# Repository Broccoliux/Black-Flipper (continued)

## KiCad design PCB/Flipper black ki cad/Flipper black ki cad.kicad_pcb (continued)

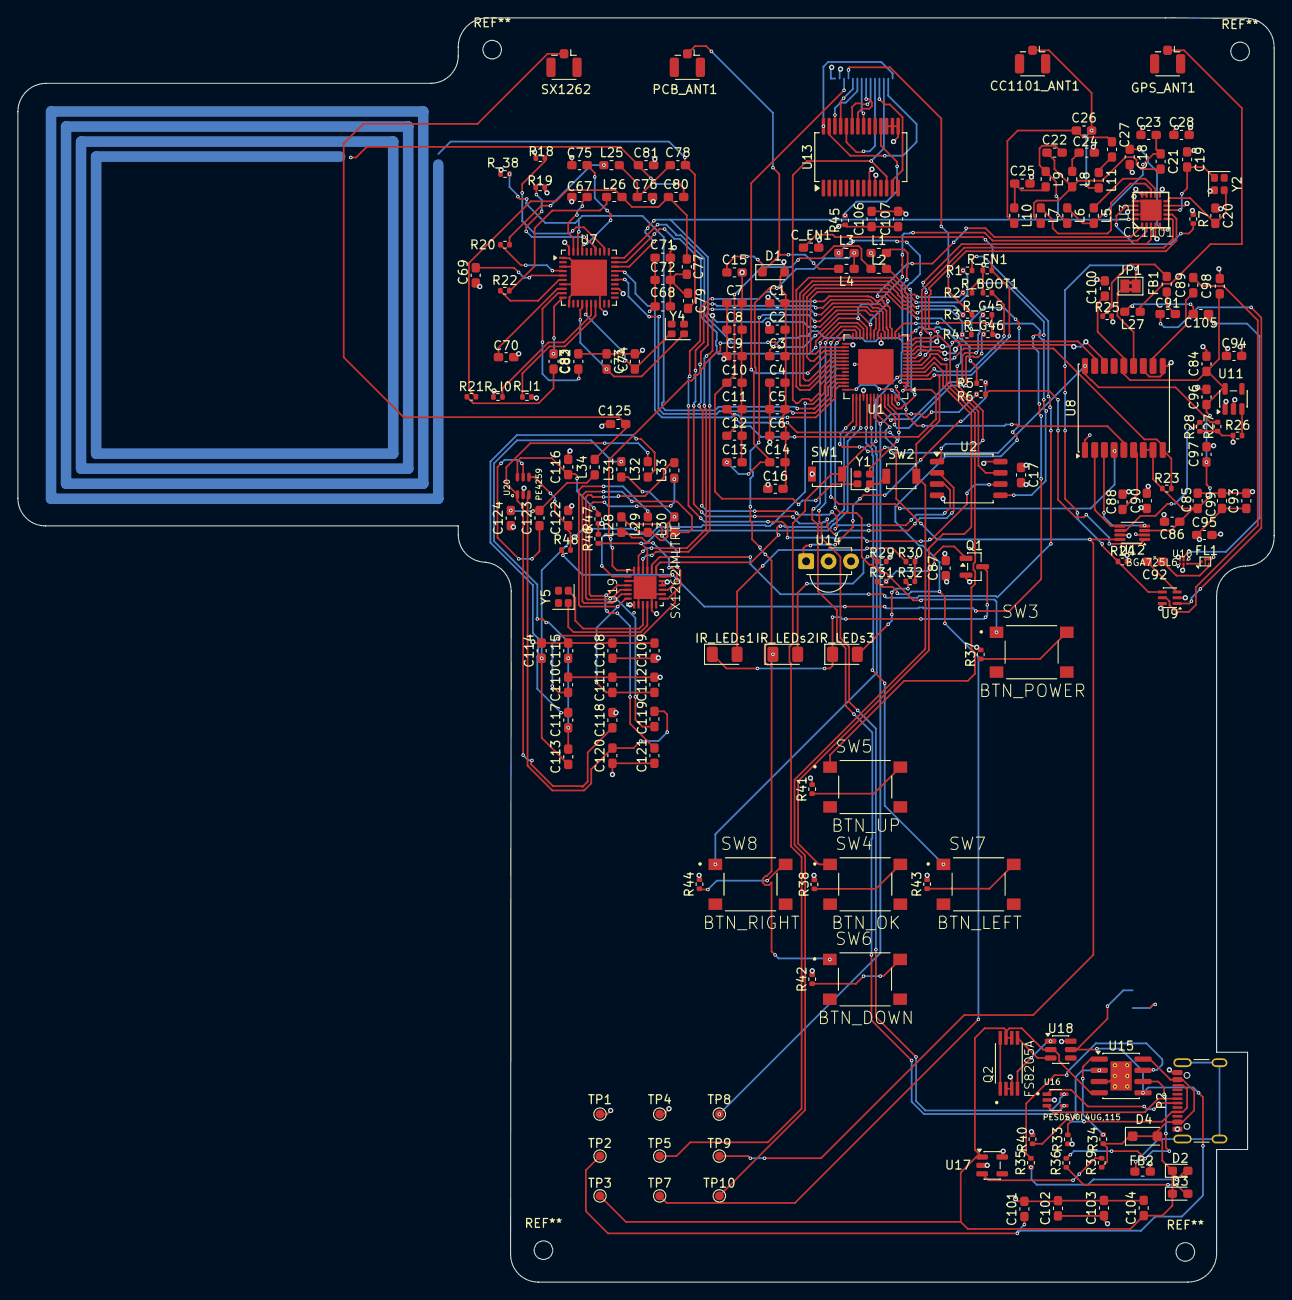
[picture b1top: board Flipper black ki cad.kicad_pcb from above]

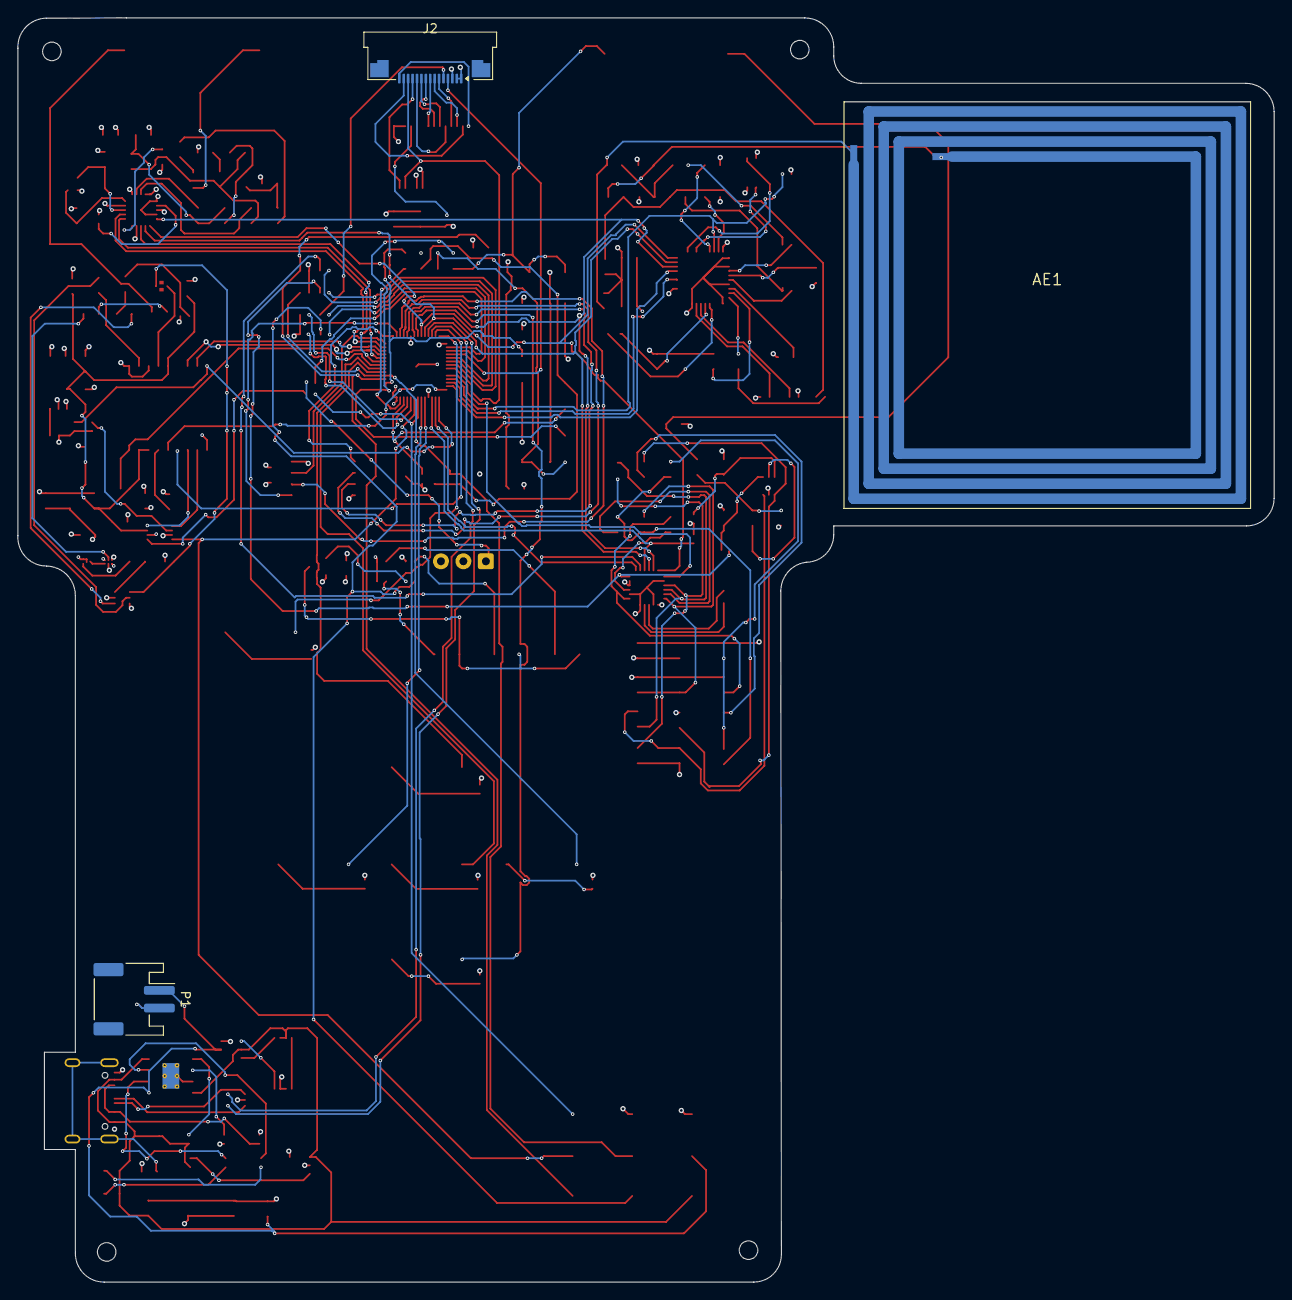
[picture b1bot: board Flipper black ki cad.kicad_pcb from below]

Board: 4 copper layers, 142.1 x 143.0 mm, 213 parts (3 on the bottom side), 169 nets.

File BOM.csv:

Reference,Qty,Value,link,cost
"C1,C2,C6,C7,C8,C17,C18,C67,C68,C69,C70,C71,C75,C84,C86,C87,C94,C96,C97,C98,C99,C100,C107,C109,C113,C121",26,100nf,,
"C3,C16,C101",3,0.1uf,,
"C4,C95,C102,C103,C104,C106",6,10uf,,
"C5,C9,C72,C85,C108,C_EN1",5,1uf,,
"C10,C11,C19,C20,C21,C22,C23,C24,C28",9,18pf,,
C12,1,1.8pf,,
C13,1,1.2pf,,
"C14,C25",2,1.0pf,,
"C15,C26,C27",3,1.5pf,,
"C74,C78,C80,C92,C119,C73",6,22pf,,
"C76,C77,C79,C81",4,220pf,,
"C82,C91,C116,C122",4,1nf,,
"C83,C105",2,100pf,,
C88,1,47pf,,
C89,1,10pf,,
"C90,C93",2,10nf,,
C110,1,470nf,,
"C111,C112,C118,C120,C123",5,10pf,,
C114,1,6.8pf,,
"C115,C125",2,8.2pf,,
"C117,C124",2,5.66pf,,
"CC1101_ANT1,GPS_ANT1,PCB_ANT1,SX1262_ANT (U.FL)",4,50ohm,,
D1,1,TPESD5V0L2,,
"D2,D3",2,LED,,
D4,1,MBR1020VL,,
"FB1,FB2",2,BLM21PG221SN1D,,
FL1,1,SAFFB1G58KA0F0A,,
"IR_LEDs1,IR_LEDs2,IR_LEDs3",3,940nm,,
J2,1,DISP_3.5_WAVESHARE,,
L1,1,2nH 500mA,,
L2,1,24nH,,
"L3,L4",2,2.7nH,,
"L5,L6,L7,L8,L32",5,27nH,,
"L9,L10",2,47nH,,
L11,1,23nH,,
"L25,L26",2,220nH,,
L27,1,5.6nH,,
"L28,L33",2,18nH,,
"L29,L30",2,15nH,,
"L31,L34",2,22nH,,
P1,1,JST-2pin,,
P2,1,USB_C_Plug_USB2.0,,
Q1,1,MMBT2222A,,
Q2,1,FS8205A,,
"R1,R2,R3,R4,R5,R_I0,R_I1",7,0R,,
R6,1,499R,,
"R7,R24,R26,R27,R34,R18,R19,R23,R28,R45,R46,R_38,R_BOOT1,R_EN1,R_G45,R_G46",15,10K,,
"R20,R22,R25,R37,R38,R41,R42,R43,R44",9,10R,,
"R21,R35,R36",3,1K,,
"R29,R30,R32",3,33R,,
"R31,R47,R48",3,100R,,
R33,1,1.2K,,
R39,1,100K,,
R40,1,5.1K,,
"SW3,4,5,6,7,8",6,BUTTONS smd,,
"SW1,2",2,IC BUTTONS,,
"TP1,2,3,4,5,6,7,8,9",5,TP HOLES,,
U1,1,ESP32-S3,,
U2,1,W25Q128JVS,,
U3,1,CC1101,,
U7,1,PN5321A3HN,,
U8,1,MAX-M8Q,,
U9,1,MASW-007221,,
U10,1,BGA725L6,,
U11,1,TLV70018_SOT23-5,,
U12,1,TXB0102DCU,,
U13,1,MCP23017x-x-SS,,
U14,1,TSOP382xx,,
U15,1,TP4056,,
U16,1,"PESD5V0L4UG,115",,
U17,1,AP2112K-3.3,,
U18,1,DW01A,,
U19,1,SX1262IMLTRT,,
U20,1,PE4259,,
Y1,1,40MHz SMD 3225,,
Y2,1,26 MHz SMD,,
Y4,1,27.120 MHz SMD,,
Y5,1,32 MHz SMD,,
ANTENNAs,1,,,
ANTENNAs,1,,,
ANTENNAs,1,,,
ANTENNAs,1,,,
mounting nuts,20,2.1mm,,
PCBA ,1,above cost wont be added if i go PCBA,,$120

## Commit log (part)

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2026-05-13 added
2026-05-13 liily
2026-05-15 SX1276
2026-05-16 guide added
2026-05-16 fahhhhhhhh
2026-05-17 les goo
2026-05-17 geoo
2026-05-17 i more done
2026-05-17 suii
2026-05-17 hnn?
2026-05-18 suiiii
2026-05-18 suiiiii
2026-05-18 fahh
2026-05-18 lololol
2026-05-18 lets gooo
2026-05-18 almost SCH done
2026-05-19 yoooo
2026-05-19 lvlvlvlv
2026-05-19 un stopable
2026-05-19 bankai
2026-05-19 suiiiiii
2026-05-19 testpoints
2026-05-19 yooooo
2026-05-19 fahhh
2026-05-19 more more more
2026-05-21 suuooooooo
2026-05-21 no finally
2026-05-22 hehe
2026-05-22 yeee
2026-05-22 yooohhohoh
2026-05-22 ahhh
2026-05-22 agg aggg
2026-05-22 rhh4i
2026-05-22 rthniew
2026-05-22 uubbj
2026-05-23 yooo
2026-05-24 zeeha
2026-05-24 krgtj
2026-05-24 yaya
2026-05-24 yayaya
2026-05-26 uuyu
2026-05-26 kdhe
2026-05-26 yayay
2026-05-26 fajhh
2026-05-26 hell
2026-05-26 ufhy
2026-05-27 hyydge
2026-05-27 sivk
2026-05-28 yehhhh
2026-05-28 zeeeee
    yayaya
2026-05-29 jjklm
2026-05-30 Big update - description of changes
2026-05-31 jjmario
2026-06-01 Rename project to 'Flipper Black' and update details
    Updated project name and description in README.md to reflect new branding and features of the Flipper Black device.
2026-06-01 Update LoRa module reference from SX1276 to SX1262
2026-06-01 Update README to clarify design origin
    Removed mention of AI-generated designs and tutorials.
2026-06-02 yruy
2026-06-02 ggklm
2026-06-02 Delete Previous Work section from README
    Removed previous work section from README.
2026-06-05 Update README with new project information
    Removed outdated project details and images, and added new project summary.
2026-06-05 Enhance README with badges and project details
    Added additional badges and expanded project description.
2026-06-05 Fix README formatting and typos
    Correct formatting of the title and fix typos in the project description.
2026-06-05 Update image descriptions in README.md
    Corrected descriptions for images and improved clarity.
2026-06-05 Update README with additional components and details
2026-06-05 Enhance README with features and component details
    Updated the README with additional details on features, components, and comparisons with Flipper Zero.
2026-06-05 Fix formatting for W25Q128 flash description
2026-06-05 Update firmware maturity status in README
2026-06-05 Update README with personal statement
    Added a personal statement and affiliation to MIT.
2026-06-05 Update Zine section with preview image
    Add a preview image for the Zine link in README
2026-06-05 Update README with Zine preview and project details
    Added a preview image link and enhanced the project description.
2026-06-05 Restore Zine section in README.md
    Reintroduced Zine section with preview link in README
2026-06-06 ggih
2026-06-08 kabooom
2026-06-09 Update Hack Club Fallout to 'shhhhhhhhh'
2026-06-19 Update README with note on content value
    Add a note about the content being expansive but worthwhile.
2026-06-24 Add assembly section to README
    Added assembly instructions for the enclosure.
2026-06-24 hunnn
2026-06-26 Add firmware submodule instructions and link to external/firmware
2026-06-26 Add .gitmodules pointing to Black-Flipper-firmware
2026-06-26 Add external/firmware README linking to firmware repo and instructions
2026-06-26 Remove firmware planned architecture details
    Removed planned architecture section for firmware from README.
2026-06-26 Update README to remove firmware development note
    Removed outdated note about firmware development status.
2026-06-26 Update README with repository structure
    Add repository structure section to README
2026-06-26 Refine project description in README.md
    Removed incomplete sentence from project description.
2026-06-26 Refine project motivation in README
    Removed trailing ellipsis from project motivation description.
